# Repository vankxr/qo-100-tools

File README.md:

# qo-100-tools
Various tools for transmission and reception on the QO-100 satellite amateur transponder bands. Includes everything I need (hopefully) to build a fully remote managed RF frontend to be placed on the roof, near the antenna while only bringing a few cables between it and the shack: power, two coax cables (TX IF and RX IF) and one UTP ethernet cable.

## Included tools
 - Upconverter - Converts the VHF/UHF IF signal to the uplink frequency of the satellite (2.4 GHz)
 - PA - Boosts the output power to 20 W (v1) and 250 W (v2) maximum
 - PA Driver - Amplifier to drive the main 250W PA
 - Directional Couplers - Experimental, manually constructed with simple scalpel cut traces on some Rogers RO4350B substrate
 - GPSDO - GPS Disciplined Oscillator to generate different precise reference frequencies
 - LNB Controller - LNB Bias and reference injection controller
 - Digital Power Meter - Module to measure DC power, used to calculate the PA efficiency
 - Digital RF Power Meter - Module to measure RF power, used to calculate the PA efficiency
 - Generic Filter - Footprints to build up to 11th order Butterworth/Chebyshev filters
 - Orange Pi Dock - Main board to house an OPi that will be the main brain of the system
 - Relay Controller - Module to provide relay coil switching capabilities
 - RF Switch - Implements a 5PST or 4PST RF switch for routing purposes
 - PSU Interface - Interface board for HP Common Slot Power supplies
 - SAW Filter adapter - Footprints for various SAW filter packages
 - PA Bias controller - Bias generator and monitor for the Power Amplifiers
 - PA TEC controller - Peltier cooler controller for the big PA
 - I2C Buffer - I2C bus signal buffer
 - Environment sensors - Sensor carrier board
 - LoRa Transceiver - SX1276 breakout for LoRa experiments

## Dependencies
 - [icyradio](https://github.com/vankxr/icyradio/tree/qo100) - IcyRadio Software Defined Radio to transmit and receive IF signals to the roof RF frontend
 - [icestorm](https://github.com/cliffordwolf/icestorm) - FPGA toolchain
 - [arm-none-eabi-gcc](https://developer.arm.com/tools-and-software/open-source-software/developer-tools/gnu-toolchain/gnu-rm/downloads) - MCUs toolchain
 - [Device CMSIS](https://www.keil.com/dd2/) - CMSIS headers defining the MCU memories, peripherals, etc...
 - [Core CMSIS](https://github.com/ARM-software/CMSIS_5) - CMSIS headers defining the ARM Cores
 - [armmem](https://github.com/vankxr/armmem) - ELF file analyzer (required for the MCU Makefiles to work)

## Authors

* **João Silva** - [vankxr](https://github.com/vankxr)

## Special thanks

* [JLCPCB](https://jlcpcb.com) for sponsoring most of the PCBs needed for this project.
* [raplin](https://github.com/raplin) for the work on [reverse engineering the HP power supplies](https://github.com/raplin/DPS-1200FB)

## License

The content of this repository is licensed under the [GNU General Public License v3.0](LICENSE).

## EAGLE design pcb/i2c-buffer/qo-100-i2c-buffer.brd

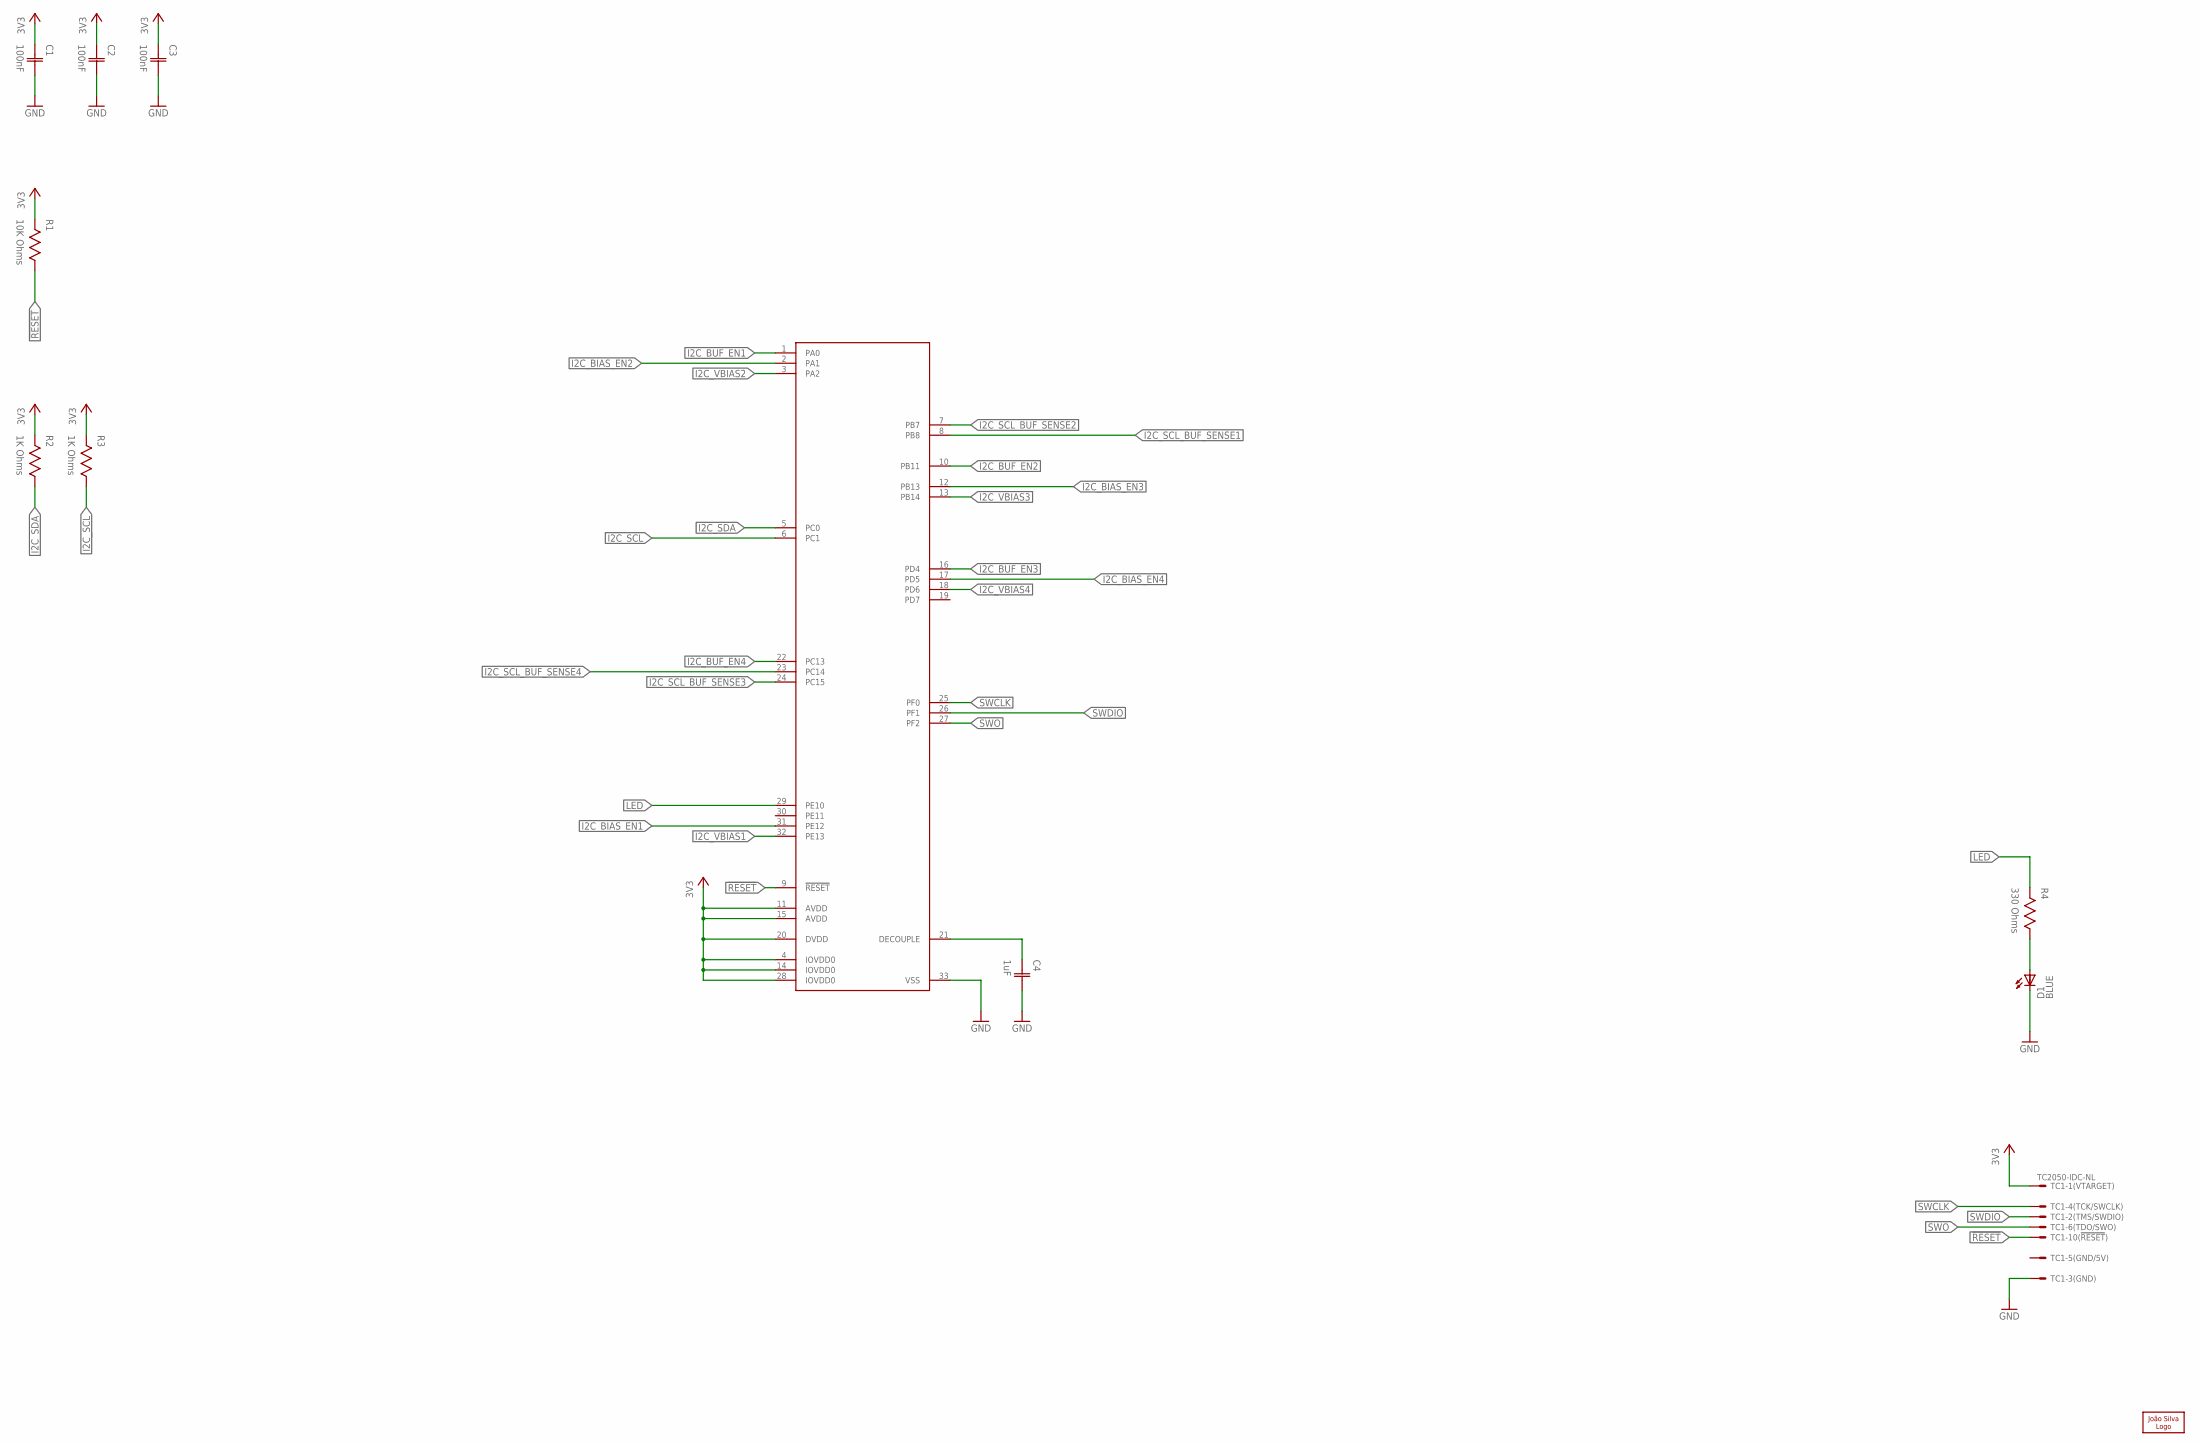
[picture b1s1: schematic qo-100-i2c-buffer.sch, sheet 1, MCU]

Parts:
C1, C2, C3: 100nF; CAP0402
C4: 1uF; CAP0402
D1: LED0603; 0603
LOGO1: JS-5MM; JS_5MM
R1: 10K Ohms; RES0402
R2, R3: 1K Ohms; RES0402
R4: 330 Ohms; RES0402
TC1: TC2050-IDC-NL
U1: EFM32TG11B120F128GM32; QFN32_0.5P_TG

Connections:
3V3: C1.1 (C1), C2.1 (C1), C3.1 (C1), R1.2, R2.2, R3.2, TC1.1, U1.4 (IOVDD0), U1.11 (AVDD), U1.14 (IOVDD0), U1.15 (AVDD), U1.20 (DVDD), U1.28 (IOVDD0); also elsewhere on the board
!RESET: R1.1, TC1.10, U1.9 (!RESET)
GND: C1.2 (C2), C2.2 (C2), C3.2 (C2), C4.2 (C2), D1.C, TC1.3, U1.33 (VSS); also elsewhere on the board
I2C_BIAS_EN1: U1.31 (PE12); also elsewhere on the board
I2C_BIAS_EN2: U1.2 (PA1); also elsewhere on the board
I2C_BIAS_EN3: U1.12 (PB13); also elsewhere on the board
I2C_BIAS_EN4: U1.17 (PD5); also elsewhere on the board
I2C_BUF_EN1: U1.1 (PA0); also elsewhere on the board
I2C_BUF_EN2: U1.10 (PB11); also elsewhere on the board
I2C_BUF_EN3: U1.16 (PD4); also elsewhere on the board
I2C_BUF_EN4: U1.22 (PC13); also elsewhere on the board
I2C_SCL: R3.1, U1.6 (PC1); also elsewhere on the board
I2C_SCL_BUF_SENSE1: U1.8 (PB8); also elsewhere on the board
I2C_SCL_BUF_SENSE2: U1.7 (PB7); also elsewhere on the board
I2C_SCL_BUF_SENSE3: U1.24 (PC15); also elsewhere on the board
I2C_SCL_BUF_SENSE4: U1.23 (PC14); also elsewhere on the board
I2C_SDA: R2.1, U1.5 (PC0); also elsewhere on the board
I2C_VBIAS1: U1.32 (PE13); also elsewhere on the board
I2C_VBIAS2: U1.3 (PA2); also elsewhere on the board
I2C_VBIAS3: U1.13 (PB14); also elsewhere on the board
I2C_VBIAS4: U1.18 (PD6); also elsewhere on the board
LED: R4.2, U1.29 (PE10)
unnamed: C4.1 (C1), U1.21 (DECOUPLE)
unnamed: D1.A, R4.1
SWCLK: TC1.4, U1.25 (PF0)
SWDIO: TC1.2, U1.26 (PF1)
SWO: TC1.6, U1.27 (PF2)

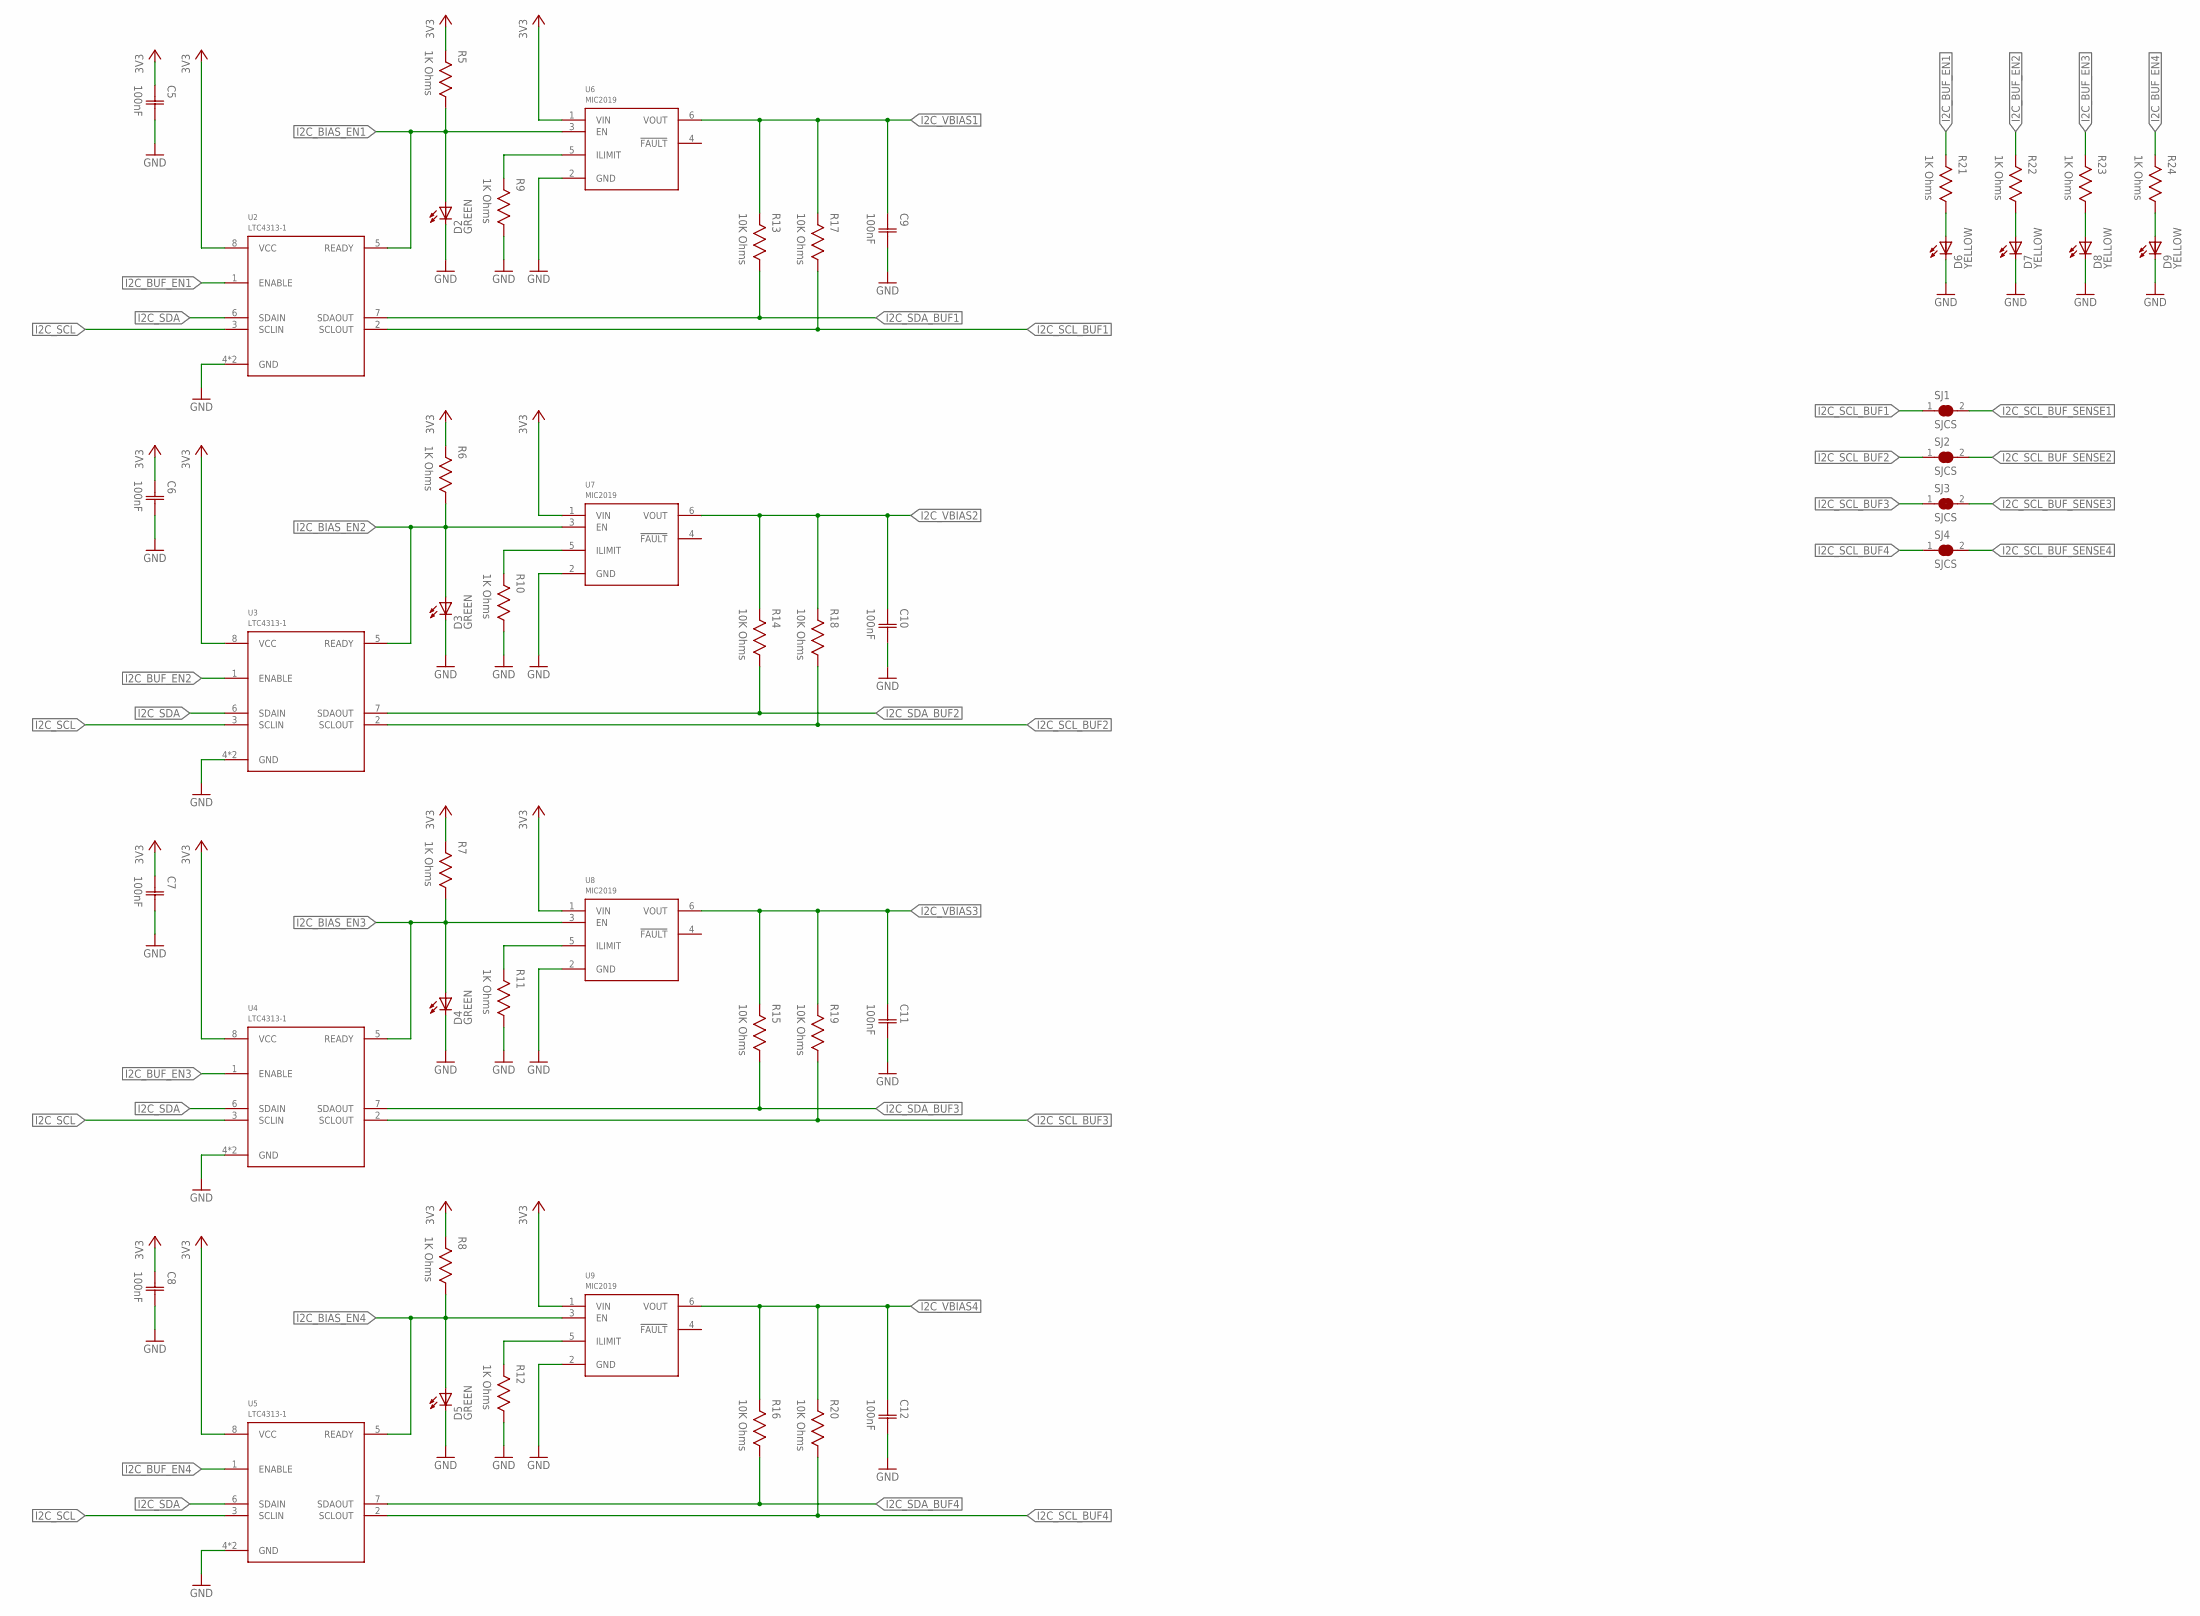
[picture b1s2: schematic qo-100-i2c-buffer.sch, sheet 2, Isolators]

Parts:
C5, C6, C7, C8, C9, C10, C11, C12: 100nF; CAP0402
D2, D3, D4, D5, D6, D7, D8, D9: LED0603; 0603
R5, R6, R7, R8, R9, R10, R11, R12, R21, R22, R23, R24: 1K Ohms; RES0402
R13, R14, R15, R16, R17, R18, R19, R20: 10K Ohms; RES0402
SJ1, SJ2, SJ3, SJ4: SJCS; SJC_S
U2, U3, U4, U5: LTC4313-1; DFN8
U6, U7, U8, U9: MIC2019; SOT23-6

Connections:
3V3: C5.1 (C1), C6.1 (C1), C7.1 (C1), C8.1 (C1), R5.2, R6.2, R7.2, R8.2, U2.8 (VCC), U3.8 (VCC), U4.8 (VCC), U5.8 (VCC), U6.1 (VIN), U7.1 (VIN), U8.1 (VIN), U9.1 (VIN); also elsewhere on the board
GND: C5.2 (C2), C6.2 (C2), C7.2 (C2), C8.2 (C2), C9.2 (C2), C10.2 (C2), C11.2 (C2), C12.2 (C2), D2.C, D3.C, D4.C, D5.C, D6.C, D7.C, D8.C, D9.C, R9.1, R10.1, R11.1, R12.1, U2.4 (GND), U2.9 (GND), U3.4 (GND), U3.9 (GND), U4.4 (GND), U4.9 (GND), U5.4 (GND), U5.9 (GND), U6.2 (GND), U7.2 (GND), U8.2 (GND), U9.2 (GND); also elsewhere on the board
I2C_BIAS_EN1: D2.A, R5.1, U2.5 (READY), U6.3 (EN); also elsewhere on the board
I2C_BIAS_EN2: D3.A, R6.1, U3.5 (READY), U7.3 (EN); also elsewhere on the board
I2C_BIAS_EN3: D4.A, R7.1, U4.5 (READY), U8.3 (EN); also elsewhere on the board
I2C_BIAS_EN4: D5.A, R8.1, U5.5 (READY), U9.3 (EN); also elsewhere on the board
I2C_BUF_EN1: R21.2, U2.1 (ENABLE); also elsewhere on the board
I2C_BUF_EN2: R22.2, U3.1 (ENABLE); also elsewhere on the board
I2C_BUF_EN3: R23.2, U4.1 (ENABLE); also elsewhere on the board
I2C_BUF_EN4: R24.2, U5.1 (ENABLE); also elsewhere on the board
I2C_SCL: U2.3 (SCLIN), U3.3 (SCLIN), U4.3 (SCLIN), U5.3 (SCLIN); also elsewhere on the board
I2C_SCL_BUF1: R17.1, SJ1.1, U2.2 (SCLOUT); also elsewhere on the board
I2C_SCL_BUF2: R18.1, SJ2.1, U3.2 (SCLOUT); also elsewhere on the board
I2C_SCL_BUF3: R19.1, SJ3.1, U4.2 (SCLOUT); also elsewhere on the board
I2C_SCL_BUF4: R20.1, SJ4.1, U5.2 (SCLOUT); also elsewhere on the board
I2C_SCL_BUF_SENSE1: SJ1.2; also elsewhere on the board
I2C_SCL_BUF_SENSE2: SJ2.2; also elsewhere on the board
I2C_SCL_BUF_SENSE3: SJ3.2; also elsewhere on the board
I2C_SCL_BUF_SENSE4: SJ4.2; also elsewhere on the board
I2C_SDA: U2.6 (SDAIN), U3.6 (SDAIN), U4.6 (SDAIN), U5.6 (SDAIN); also elsewhere on the board
I2C_SDA_BUF1: R13.1, U2.7 (SDAOUT); also elsewhere on the board
I2C_SDA_BUF2: R14.1, U3.7 (SDAOUT); also elsewhere on the board
I2C_SDA_BUF3: R15.1, U4.7 (SDAOUT); also elsewhere on the board
I2C_SDA_BUF4: R16.1, U5.7 (SDAOUT); also elsewhere on the board
I2C_VBIAS1: C9.1 (C1), R13.2, R17.2, U6.6 (VOUT); also elsewhere on the board
I2C_VBIAS2: C10.1 (C1), R14.2, R18.2, U7.6 (VOUT); also elsewhere on the board
I2C_VBIAS3: C11.1 (C1), R15.2, R19.2, U8.6 (VOUT); also elsewhere on the board
I2C_VBIAS4: C12.1 (C1), R16.2, R20.2, U9.6 (VOUT); also elsewhere on the board
unnamed: R9.2, U6.5 (ILIMIT)
unnamed: R10.2, U7.5 (ILIMIT)
unnamed: R11.2, U8.5 (ILIMIT)
unnamed: R12.2, U9.5 (ILIMIT)
unnamed: D6.A, R21.1
unnamed: D7.A, R22.1
unnamed: D8.A, R23.1
unnamed: D9.A, R24.1

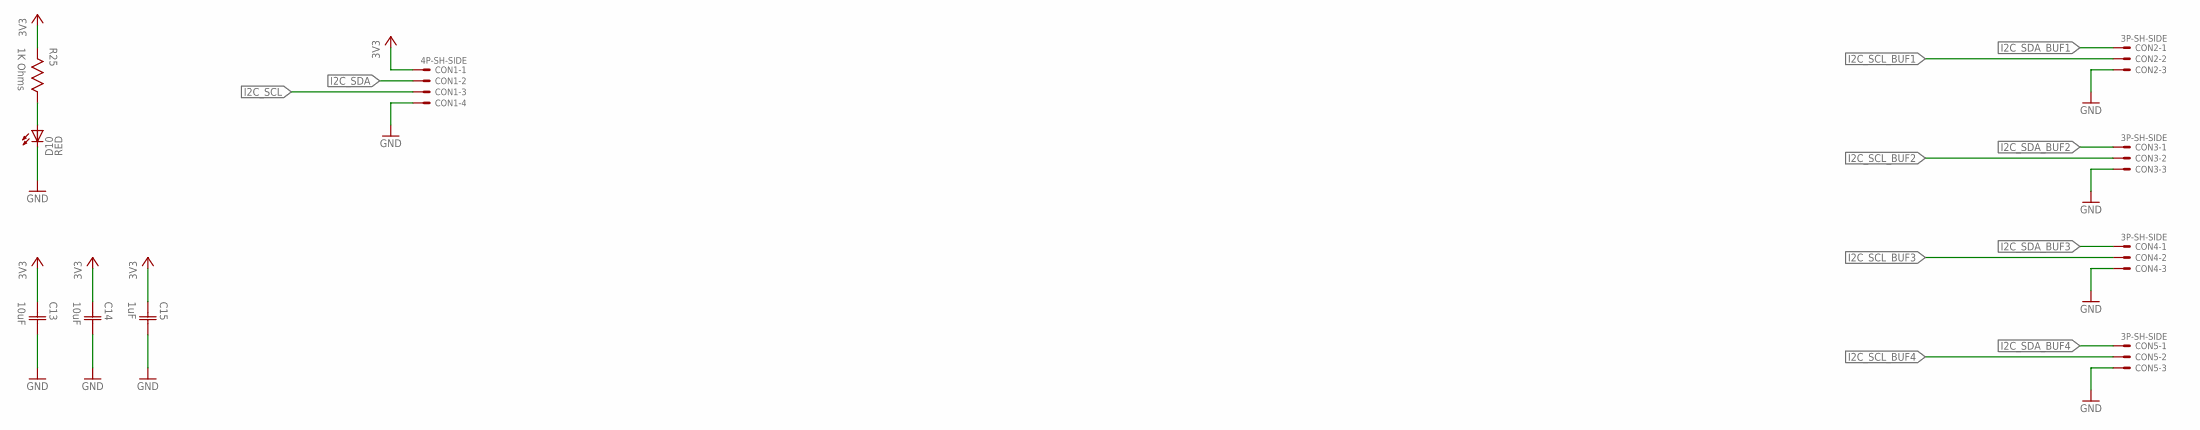
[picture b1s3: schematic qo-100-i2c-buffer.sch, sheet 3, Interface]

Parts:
C13, C14: 10uF; CAP0603
C15: 1uF; CAP0402
CON1: 4P-SH-SIDE; SH-04-SIDE
CON2, CON3, CON4, CON5: 3P-SH-SIDE; SH-03-SIDE
D10: LED0603; 0603
R25: 1K Ohms; RES0402

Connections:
3V3: C13.1 (C1), C14.1 (C1), C15.1 (C1), CON1.1, R25.2; also elsewhere on the board
GND: C13.2 (C2), C14.2 (C2), C15.2 (C2), CON1.4, CON2.3, CON3.3, CON4.3, CON5.3, D10.C; also elsewhere on the board
I2C_SCL: CON1.3; also elsewhere on the board
I2C_SCL_BUF1: CON2.2; also elsewhere on the board
I2C_SCL_BUF2: CON3.2; also elsewhere on the board
I2C_SCL_BUF3: CON4.2; also elsewhere on the board
I2C_SCL_BUF4: CON5.2; also elsewhere on the board
I2C_SDA: CON1.2; also elsewhere on the board
I2C_SDA_BUF1: CON2.1; also elsewhere on the board
I2C_SDA_BUF2: CON3.1; also elsewhere on the board
I2C_SDA_BUF3: CON4.1; also elsewhere on the board
I2C_SDA_BUF4: CON5.1; also elsewhere on the board
unnamed: D10.A, R25.1

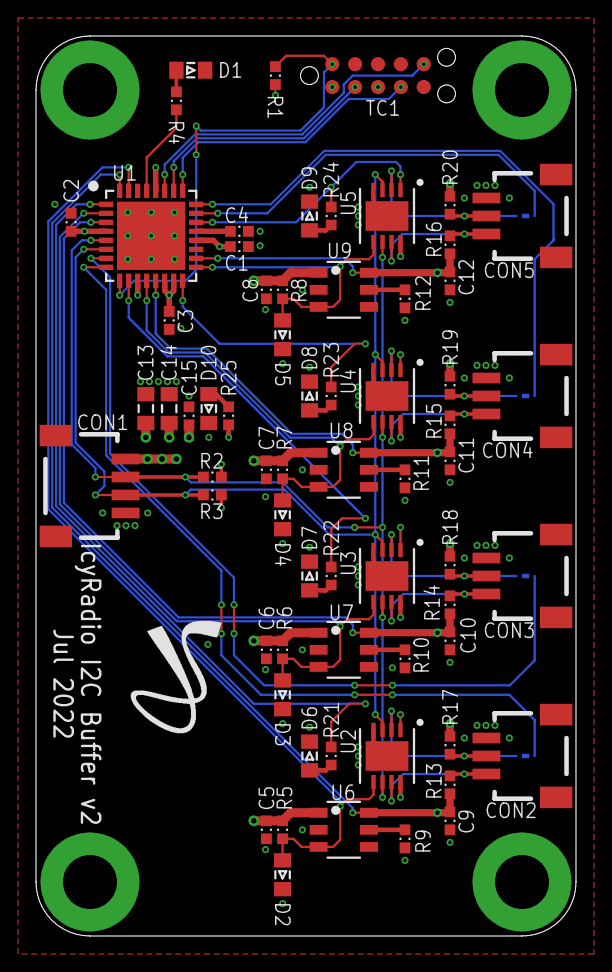
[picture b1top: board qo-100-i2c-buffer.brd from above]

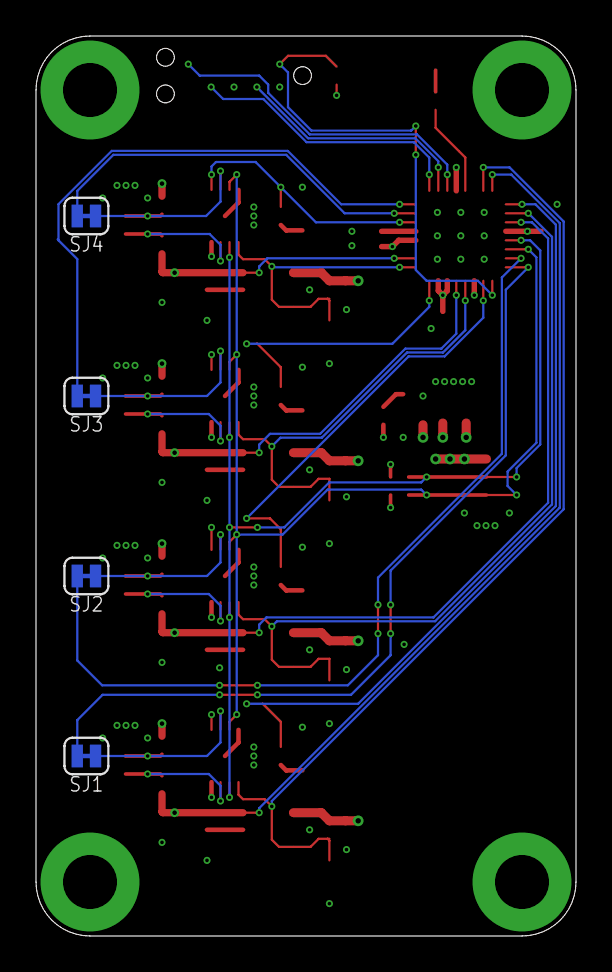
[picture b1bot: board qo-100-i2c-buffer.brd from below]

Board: 4 copper layers, 30.0 x 50.0 mm, 70 parts (4 on the bottom side), 44 nets.

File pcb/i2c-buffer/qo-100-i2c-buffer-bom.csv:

Comment,Footprint,Designator
100nF,CAP0402,"C1, C2, C3, C5, C6, C7, C8, C9, C10, C11, C12"
10K Ohms,RES0402,"R1, R13, R14, R15, R16, R17, R18, R19, R20"
10uF,CAP0603,"C13, C14"
1K Ohms,RES0402,"R2, R3, R5, R6, R7, R8, R9, R10, R11, R12, R21, R22, R23, R24, R25"
1uF,CAP0402,"C4, C15"
330 Ohms,RES0402,R4
LED0603,0603,D1
LED0603,0603,"D2, D3, D4, D5"
LED0603,0603,D10
LED0603,0603,"D6, D7, D8, D9"

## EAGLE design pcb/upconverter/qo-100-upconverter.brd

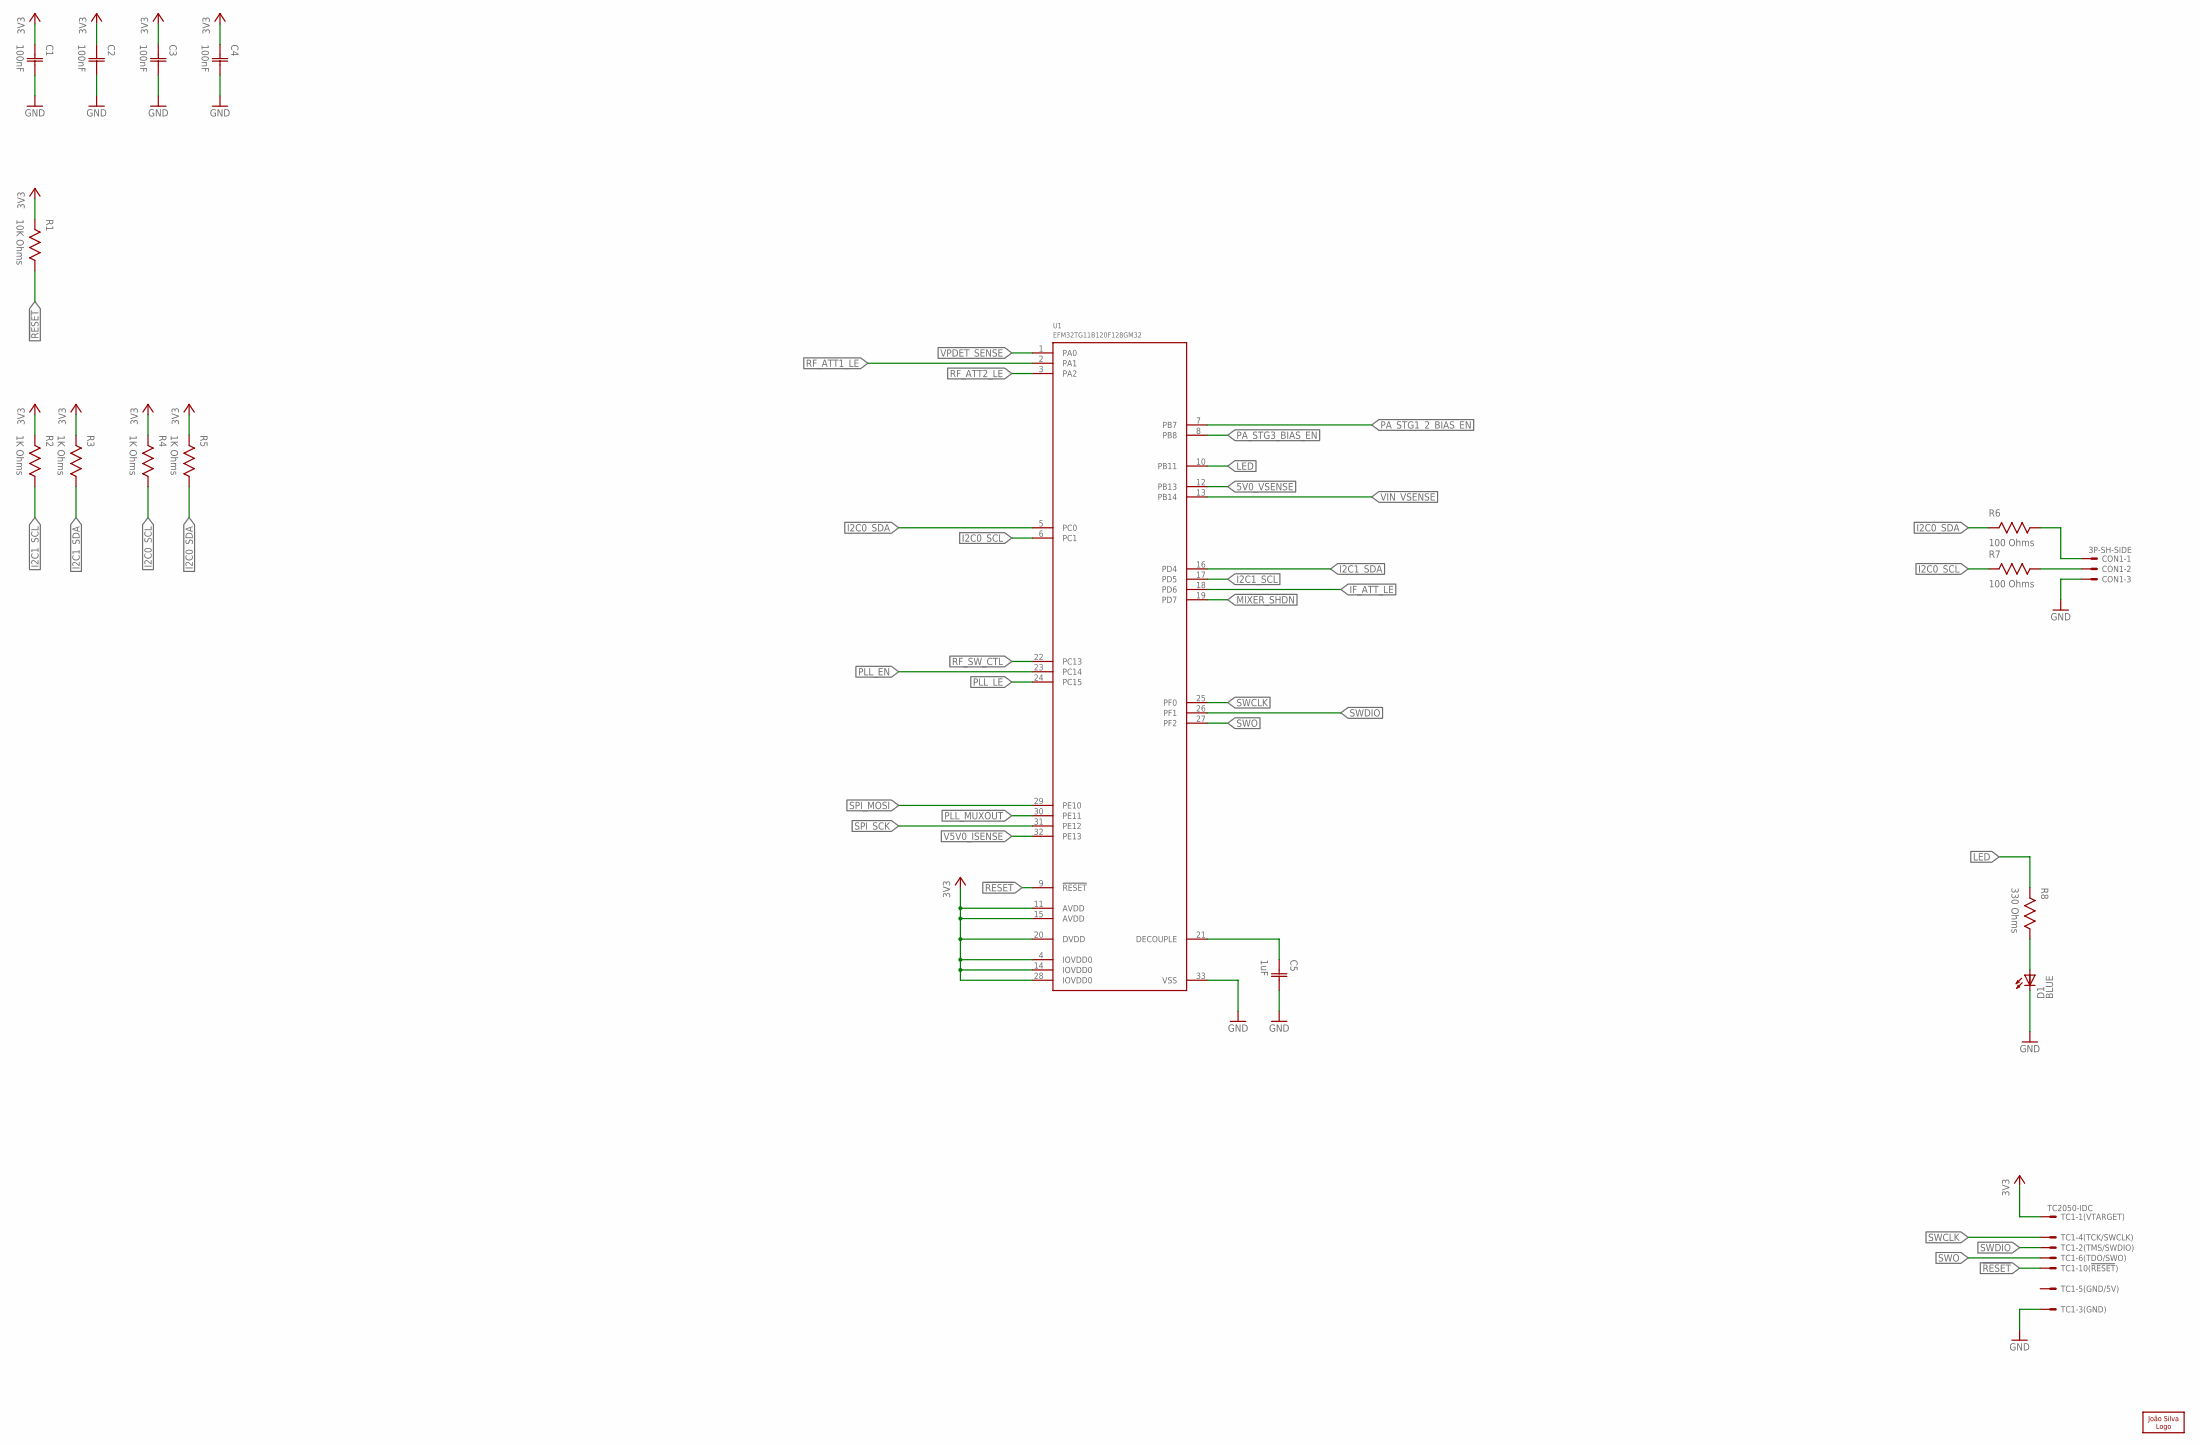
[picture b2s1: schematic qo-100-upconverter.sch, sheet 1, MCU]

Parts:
C1, C2, C3, C4: 100nF; CAP0603
C5: 1uF; CAP0603
CON1: 3P-SH-SIDE; SH-03-SIDE
D1: LED0603; 0603
LOGO1: JS-5MM; JS_5MM
R1: 10K Ohms; RES0603
R2, R3, R4, R5: 1K Ohms; RES0603
R6, R7: 100 Ohms; RES0603
R8: 330 Ohms; RES0603
TC1: TC2050-IDC
U1: EFM32TG11B120F128GM32; QFN32_0.5P_TG

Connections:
3V3: C1.1 (C1), C2.1 (C1), C3.1 (C1), C4.1 (C1), R1.2, R2.2, R3.2, R4.2, R5.2, TC1.1, U1.4 (IOVDD0), U1.11 (AVDD), U1.14 (IOVDD0), U1.15 (AVDD), U1.20 (DVDD), U1.28 (IOVDD0); also elsewhere on the board
5V0_VSENSE: U1.12 (PB13); also elsewhere on the board
!MIXER_SHDN: U1.19 (PD7); also elsewhere on the board
!RESET: R1.1, TC1.10, U1.9 (!RESET)
GND: C1.2 (C2), C2.2 (C2), C3.2 (C2), C4.2 (C2), C5.2 (C2), CON1.3, D1.C, TC1.3, U1.33 (VSS); also elsewhere on the board
I2C0_SCL: R4.1, R7.2, U1.6 (PC1)
I2C0_SDA: R5.1, R6.2, U1.5 (PC0)
I2C1_SCL: R2.1, U1.17 (PD5); also elsewhere on the board
I2C1_SDA: R3.1, U1.16 (PD4); also elsewhere on the board
IF_ATT_LE: U1.18 (PD6); also elsewhere on the board
LED: R8.2, U1.10 (PB11)
unnamed: CON1.2, R7.1
unnamed: CON1.1, R6.1
unnamed: C5.1 (C1), U1.21 (DECOUPLE)
unnamed: D1.A, R8.1
PA_STG1_2_BIAS_EN: U1.7 (PB7); also elsewhere on the board
PA_STG3_BIAS_EN: U1.8 (PB8); also elsewhere on the board
PLL_EN: U1.23 (PC14); also elsewhere on the board
PLL_LE: U1.24 (PC15); also elsewhere on the board
PLL_MUXOUT: U1.30 (PE11); also elsewhere on the board
RF_ATT1_LE: U1.2 (PA1); also elsewhere on the board
RF_ATT2_LE: U1.3 (PA2); also elsewhere on the board
RF_SW_CTL: U1.22 (PC13); also elsewhere on the board
SPI_MOSI: U1.29 (PE10); also elsewhere on the board
SPI_SCK: U1.31 (PE12); also elsewhere on the board
SWCLK: TC1.4, U1.25 (PF0)
SWDIO: TC1.2, U1.26 (PF1)
SWO: TC1.6, U1.27 (PF2)
V5V0_ISENSE: U1.32 (PE13); also elsewhere on the board
VIN_VSENSE: U1.13 (PB14); also elsewhere on the board
VPDET_SENSE: U1.1 (PA0); also elsewhere on the board

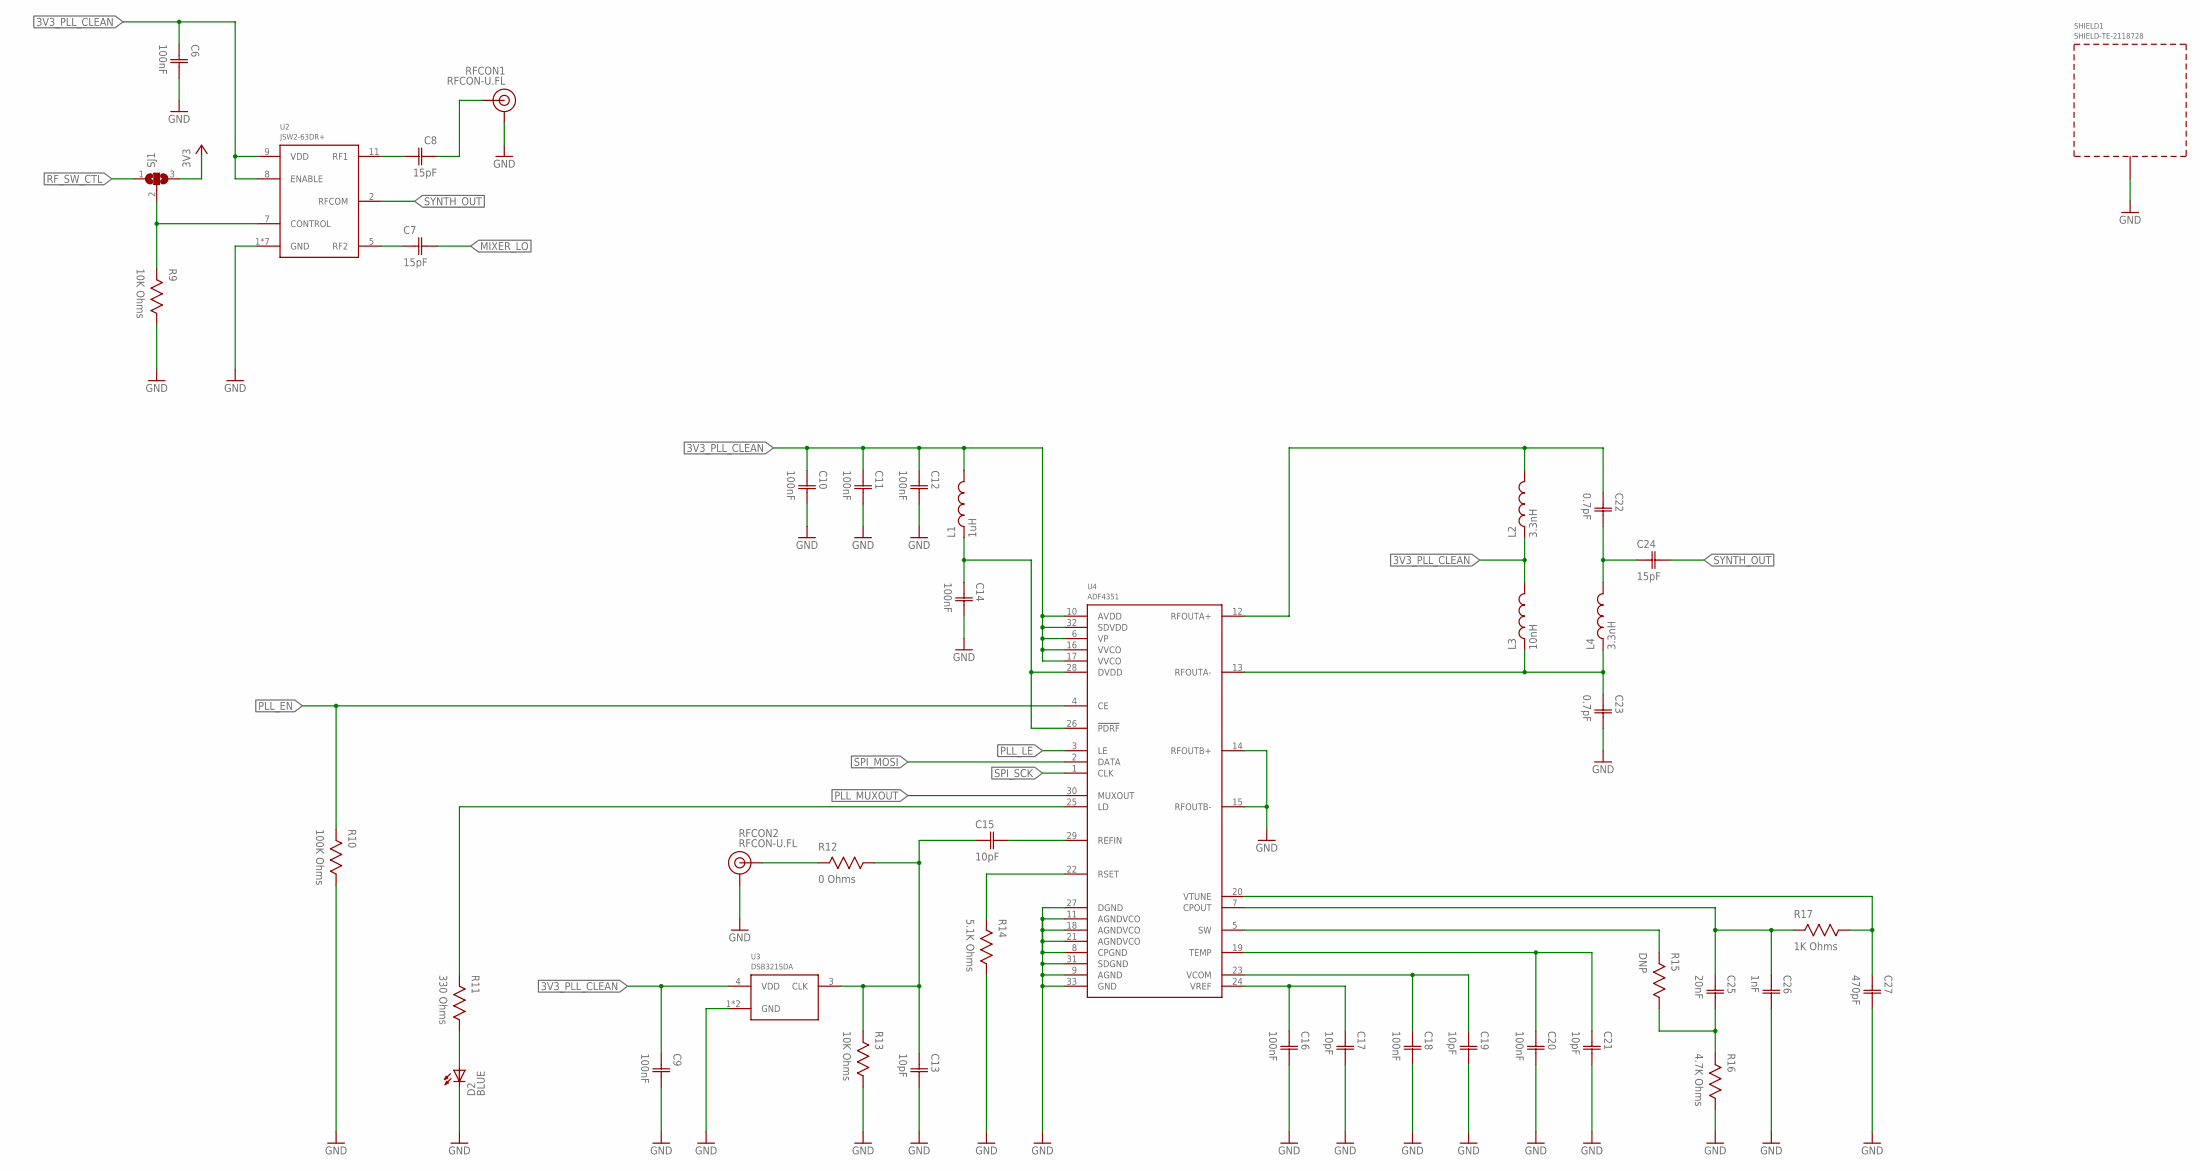
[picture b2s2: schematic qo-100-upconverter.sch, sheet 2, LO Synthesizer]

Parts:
C6, C9, C10, C11, C12, C14, C16, C18, C20: 100nF; CAP0603
C7, C8, C24: 15pF; CAP0603
C13, C15, C17, C19, C21: 10pF; CAP0603
C22, C23: 0.7pF; CAP0603
C25: 20nF; CAP0603
C26: 1nF; CAP0603
C27: 470pF; CAP0603
D2: LED0603; 0603
L1: 1uH; IND0603
L2, L4: 3.3nH; IND0603
L3: 10nH; IND0603
R9, R13: 10K Ohms; RES0603
R10: 100K Ohms; RES0603
R11: 330 Ohms; RES0603
R12: 0 Ohms; RES0603
R14: 5.1K Ohms; RES0603
R15: DNP; RES0603
R16: 4.7K Ohms; RES0603
R17: 1K Ohms; RES0603
RFCON1, RFCON2: RFCON-U.FL; U.FL
SHIELD1: SHIELD-TE-2118728; 2118728
SJ1: SJ2S; SJ2_S
U2: JSW2-63DR+; MT1818
U3: DSB321SDA; TCXO-3225
U4: ADF4351; QFN32

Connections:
3V3: SJ1.3; also elsewhere on the board
3V3_PLL_CLEAN: C6.1 (C1), C9.1 (C1), C10.1 (C1), C11.1 (C1), C12.1 (C1), L1.2, L2.1, L3.2, U2.8 (ENABLE), U2.9 (VDD), U3.4 (VDD), U4.6 (VP), U4.10 (AVDD), U4.16 (VVCO), U4.17 (VVCO), U4.32 (SDVDD); also elsewhere on the board
GND: C6.2 (C2), C9.2 (C2), C10.2 (C2), C11.2 (C2), C12.2 (C2), C13.2 (C2), C14.2 (C2), C16.2 (C2), C17.2 (C2), C18.2 (C2), C19.2 (C2), C20.2 (C2), C21.2 (C2), C23.2 (C2), C26.2 (C2), C27.2 (C2), D2.C, R9.1, R10.1, R13.1, R14.1, R16.1, RFCON1.P$1 (GND), RFCON1.P$2 (GND), RFCON2.P$1 (GND), RFCON2.P$2 (GND), SHIELD1.1, SHIELD1.2, SHIELD1.3, SHIELD1.4, SHIELD1.5, SHIELD1.6, SHIELD1.7, SHIELD1.8, SHIELD1.9, SHIELD1.10, SHIELD1.11, SHIELD1.12, SHIELD1.13, SHIELD1.14, SHIELD1.15, SHIELD1.16, U2.1 (GND), U2.3 (GND), U2.4 (GND), U2.6 (GND), U2.10 (GND), U2.12 (GND), U2.17 (GND), U3.1 (GND), U3.2 (GND), U4.8 (CPGND), U4.9 (AGND), U4.11 (AGNDVCO), U4.14 (RFOUTB+), U4.15 (RFOUTB-), U4.18 (AGNDVCO), U4.21 (AGNDVCO), U4.27 (DGND), U4.31 (SDGND), U4.33 (GND); also elsewhere on the board
LO_OUT: C8.1 (C1), RFCON1.P$3 (SIGNAL)
LO_SW_CTL: R9.2, SJ1.2, U2.7 (CONTROL)
MIXER_LO: C7.2 (C2); also elsewhere on the board
unnamed: C22.2 (C2), C24.1 (C1), L4.2
unnamed: C14.1 (C1), L1.1, U4.26 (!PDRF), U4.28 (DVDD)
unnamed: C7.1 (C1), U2.5 (RF2)
unnamed: D2.A, R11.1
unnamed: C8.2 (C2), U2.11 (RF1)
unnamed: R12.2, RFCON2.P$3 (SIGNAL)
unnamed: C23.1 (C1), L3.1, L4.1, U4.13 (RFOUTA-)
unnamed: C22.1 (C1), L2.2, U4.12 (RFOUTA+)
unnamed: C25.2 (C2), R15.1, R16.2
unnamed: R14.2, U4.22 (RSET)
PLL_CP_VOUT: C25.1 (C1), C26.1 (C1), R17.2, U4.7 (CPOUT)
PLL_EN: R10.2, U4.4 (CE); also elsewhere on the board
PLL_FASTLOCK_SW: R15.2, U4.5 (SW)
PLL_LE: U4.3 (LE); also elsewhere on the board
PLL_LOCK: R11.2, U4.25 (LD)
PLL_MUXOUT: U4.30 (MUXOUT); also elsewhere on the board
PLL_REF_ACC: C15.2 (C2), U4.29 (REFIN)
PLL_REF_DCC: C13.1 (C1), C15.1 (C1), R12.1, R13.2, U3.3 (CLK)
PLL_TEMP: C20.1 (C1), C21.1 (C1), U4.19 (TEMP)
PLL_VCOM: C18.1 (C1), C19.1 (C1), U4.23 (VCOM)
PLL_VREF: C16.1 (C1), C17.1 (C1), U4.24 (VREF)
PLL_VTUNE: C27.1 (C1), R17.1, U4.20 (VTUNE)
RF_SW_CTL: SJ1.1; also elsewhere on the board
SPI_MOSI: U4.2 (DATA); also elsewhere on the board
SPI_SCK: U4.1 (CLK); also elsewhere on the board
SYNTH_OUT: C24.2 (C2), U2.2 (RFCOM)
